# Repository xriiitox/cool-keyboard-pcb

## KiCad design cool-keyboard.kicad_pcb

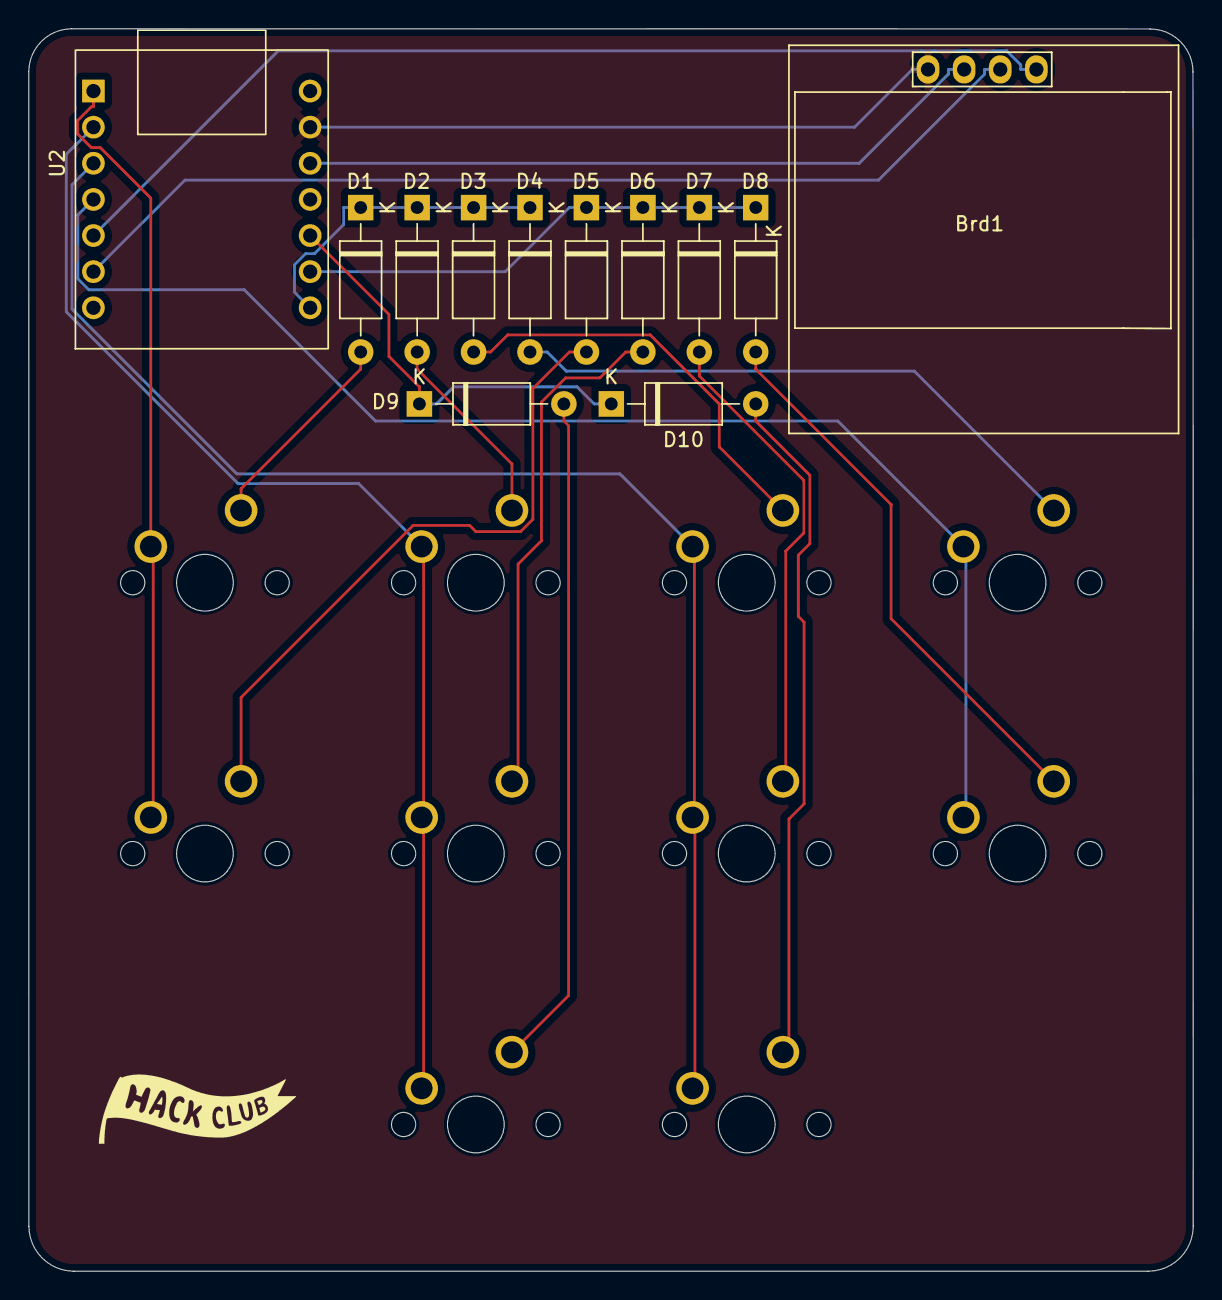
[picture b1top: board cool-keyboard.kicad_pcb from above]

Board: 2 copper layers, 81.9 x 87.4 mm, 22 parts (0 on the bottom side), 21 nets.

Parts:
Brd1: SSD1306; 128x64OLED
D1, D2, D3, D4, D5, D6, D7, D8, D9, D10: D; D_A-405_P10.16mm_Horizontal
SW1, SW2, SW3, SW4, SW5, SW6, SW7, SW8, SW9, SW10: SW_Push_45deg; MX-Solderable-1U
U2: MOUDLE-SEEEDUINO-XIAO; MOUDLE14P-2.54-21X17.8MM

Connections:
COL0: SW1.1, SW5.1, U2.1 (PA02_A0_D0)
COL1: SW2.1, SW6.1, SW9.1, U2.2 (PA4_A1_D1)
COL2: SW3.1, SW7.1, SW10.1, U2.3 (PA10_A2_D2)
COL3: SW4.1, SW8.1, U2.4 (PA11_A3_D3)
GND: Brd1.1 (GND), U2.13 (GND)
unnamed: Brd1.3 (SCL), U2.6 (PA9_A5_D5_SCL)
unnamed: Brd1.4 (SDA), U2.5 (PA8_A4_D4_SDA)
unnamed: D1.2 (A), SW1.2
unnamed: D2.2 (A), SW2.2
unnamed: D3.2 (A), SW3.2
unnamed: D4.2 (A), SW4.2
unnamed: D5.2 (A), SW5.2
unnamed: D6.2 (A), SW6.2
unnamed: D7.2 (A), SW7.2
unnamed: D8.2 (A), SW8.2
unnamed: D9.2 (A), SW9.2
unnamed: D10.2 (A), SW10.2
ROW0: D1.1 (K), D2.1 (K), D3.1 (K), D4.1 (K), U2.8 (PB09_A7_D7_RX)
ROW1: D5.1 (K), D6.1 (K), D7.1 (K), D8.1 (K), U2.9 (PA7_A8_D8_SCK)
ROW2: D9.1 (K), D10.1 (K), U2.10 (PA5_A9_D9_MISO)
SCR3V3: Brd1.2 (VCC), U2.12 (3V3)

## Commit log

2024-09-10 Add submodules
2024-09-10 add footprint libraries
2024-09-10 add rp2040 footprint
2024-09-10 schematic gaming
2024-09-11 update schematic
2024-09-14 finish sch + basic pcb
2024-09-14 traces
2024-09-14 drc errors
    a couple silkscreen overlaps, just wanted to fix them for completion's sake
2024-09-15 fix mcu placement
2024-09-16 add ssd1306
2024-09-17 3d screen + design fix
2024-09-17 add step
2024-09-18 add models for switches
2024-09-21 add ground fill
2024-09-22 add firmware
